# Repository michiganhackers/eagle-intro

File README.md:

eagle-intro
===========

Companion to https://www.facebook.com/events/484634361585476/

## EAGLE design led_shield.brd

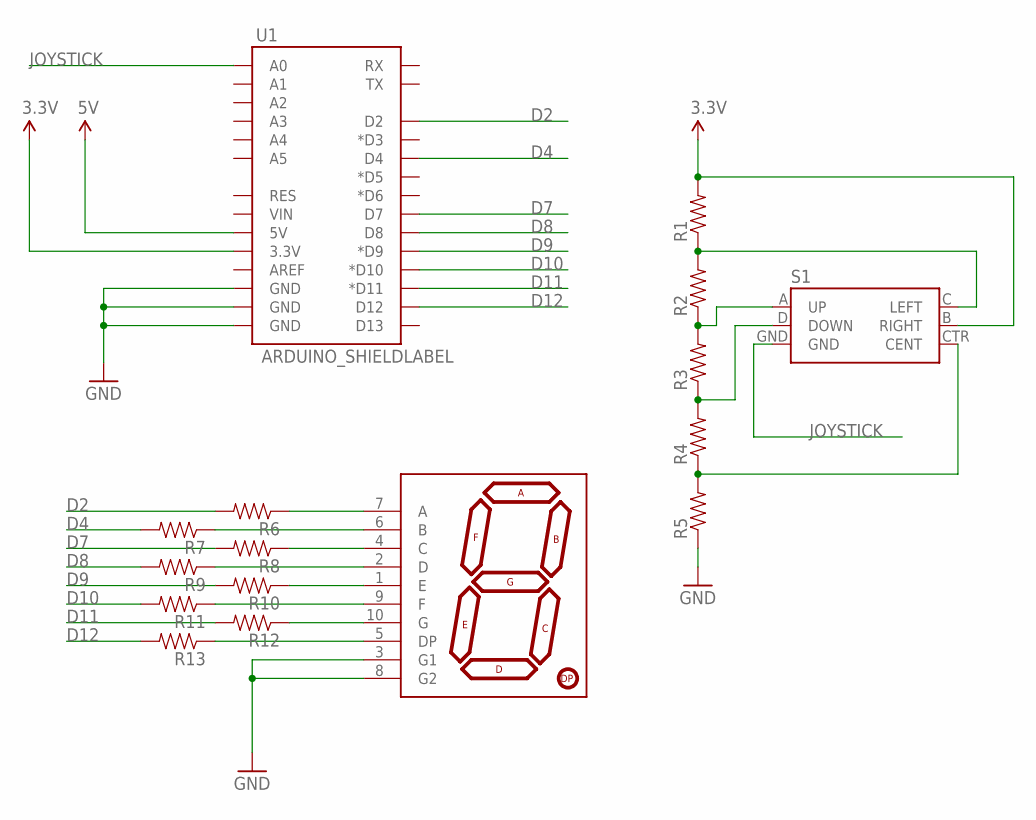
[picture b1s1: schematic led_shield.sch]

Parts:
R1, R2, R3, R4, R5, R6, R7, R8, R9, R10, R11, R12, R13: RESISTOR0805-RES; 0805
S1: JOYSTICK_MINI
U1: ARDUINO_SHIELDLABEL; DUEMILANOVE_SHIELD
U$1: 7-SEGMENT-DISPLAY-1"-RED; 7-SEGMENT-1"PTH

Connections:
3.3V: R1.2, S1.B (RIGHT), U1.3.3V
5V: U1.5V
D2: R6.2, U1.D2
D4: R7.2, U1.D4
D7: R8.2, U1.D7
D8: R9.2, U1.D8
D9: R10.2, U1.D9 (*D9)
D10: R11.2, U1.D10 (*D10)
D11: R12.2, U1.D11 (*D11)
D12: R13.2, U1.D12
GND: R5.1, U1.GND@0 (GND), U1.GND@1 (GND), U1.GND@2 (GND), U$1.3 (G1), U$1.8 (G2)
JOYSTICK: S1.GND, U1.A0
unnamed: R1.1, R2.2, S1.C (LEFT)
unnamed: R6.1, U$1.7 (A)
unnamed: R2.1, R3.2, S1.A (UP)
unnamed: R3.1, R4.2, S1.D (DOWN)
unnamed: R4.1, R5.2, S1.CTR (CENT)
unnamed: R7.1, U$1.6 (B)
unnamed: R8.1, U$1.4 (C)
unnamed: R9.1, U$1.2 (D)
unnamed: R10.1, U$1.1 (E)
unnamed: R11.1, U$1.9 (F)
unnamed: R12.1, U$1.10 (G)
unnamed: R13.1, U$1.5 (DP)

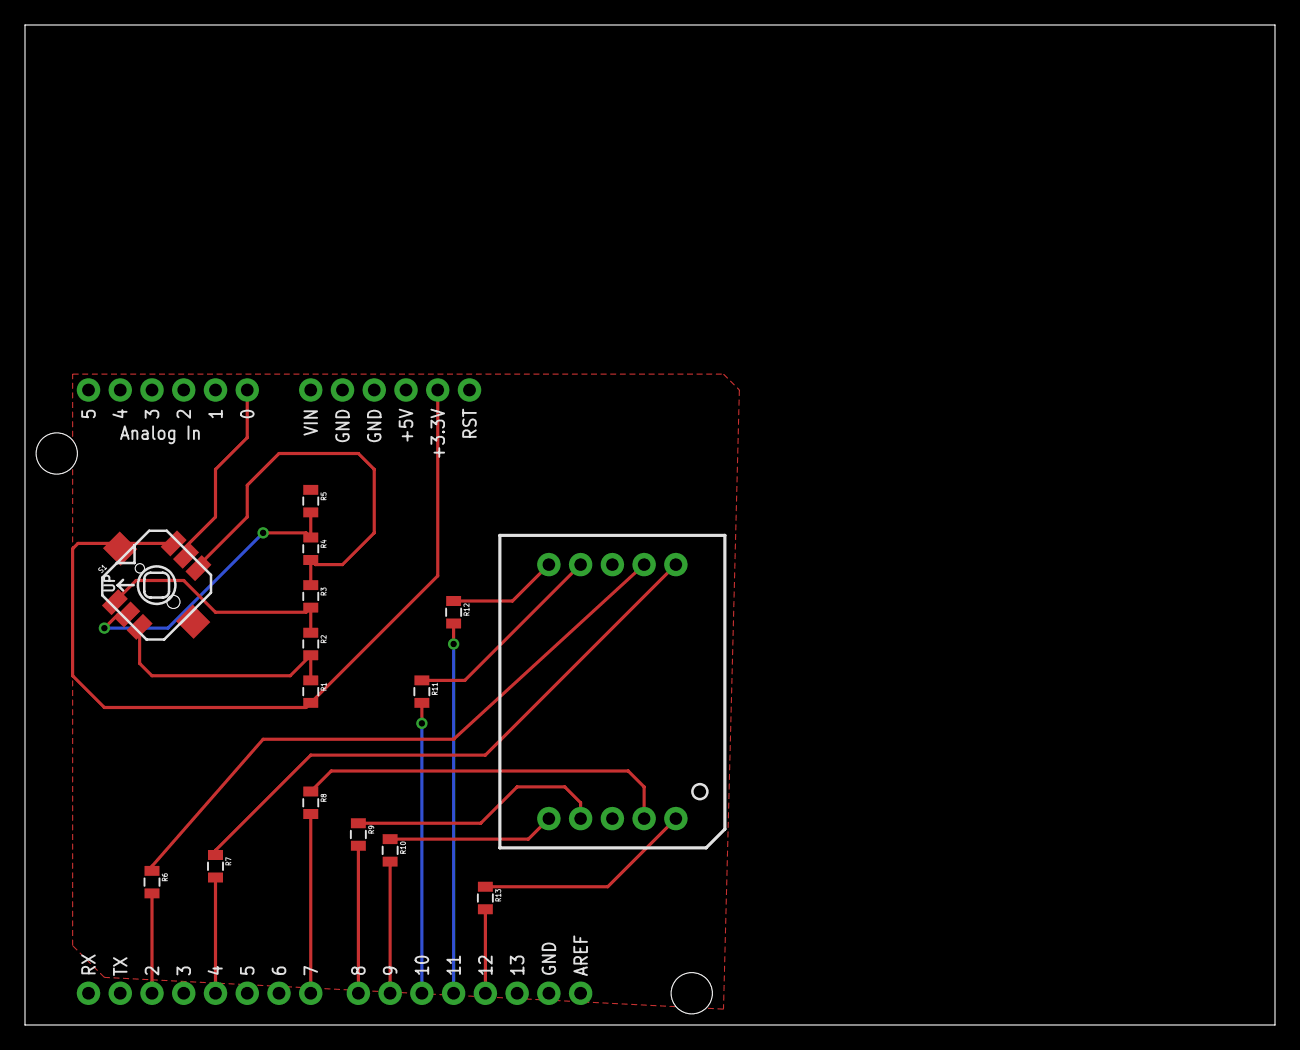
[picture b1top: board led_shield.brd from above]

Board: 2 copper layers, 100.0 x 80.0 mm, 16 parts (0 on the bottom side), 23 nets.

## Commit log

2013-03-19 Creating repo for Eagle Intro Talk

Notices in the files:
parts and their libraries:
SparkFun-Boards: Licensing: CC v3.0 Share-Alike You are welcome to use this library for commercial purposes.
